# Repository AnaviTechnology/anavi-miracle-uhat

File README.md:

# ANAVI Miracle uHAT

ANAVI Miracle uHAT is an open source hardware Raspberry Pi add-on board for controlling NeoPixel RGB LED strip powered by free and open source software. It features:

* Slot for addressable NeoPixel RGB LED strip like WS2812B, WS2812B, WS2811, etc.
* Power input barrel jack for the addressable RGB LED strip
* Slot for PIR motion sensor
* Slot for I2C mini OLED display
* Slots for up to 3 plug and play I2C sensors for temperature, barometric pressure, humidity and light
* UART (Universal asynchronous receiver/transmitter) pins for debugging
* EEPROM

# License

The project is released under the [Creative Commons Attribution-ShareAlike 4.0 International (CC BY-SA 4.0)](https://creativecommons.org/licenses/by-sa/4.0/).

Note: This is a human-readable summary of (and not a substitute for) the [license](https://creativecommons.org/licenses/by-sa/4.0/legalcode).

You are free to:

Share — copy and redistribute the material in any medium or format Adapt — remix, transform, and build upon the material for any purpose, even commercially. The licensor cannot revoke these freedoms as long as you follow the license terms. Under the following terms:

Attribution — You must give appropriate credit, provide a link to the license, and indicate if changes were made. You may do so in any reasonable manner, but not in any way that suggests the licensor endorses you or your use. ShareAlike — If you remix, transform, or build upon the material, you must distribute your contributions under the same license as the original. No additional restrictions — You may not apply legal terms or technological measures that legally restrict others from doing anything the license permits. Notices:

You do not have to comply with the license for elements of the material in the public domain or where your use is permitted by an applicable exception or limitation. No warranties are given. The license may not give you all of the permissions necessary for your intended use. For example, other rights such as publicity, privacy, or moral rights may limit how you use the material.

You will have to provide a link to the original creator of the project https://www.anavi.technology on any documentation or website.

Credit can be attributed through a link to the creator website: https://www.anavi.technology

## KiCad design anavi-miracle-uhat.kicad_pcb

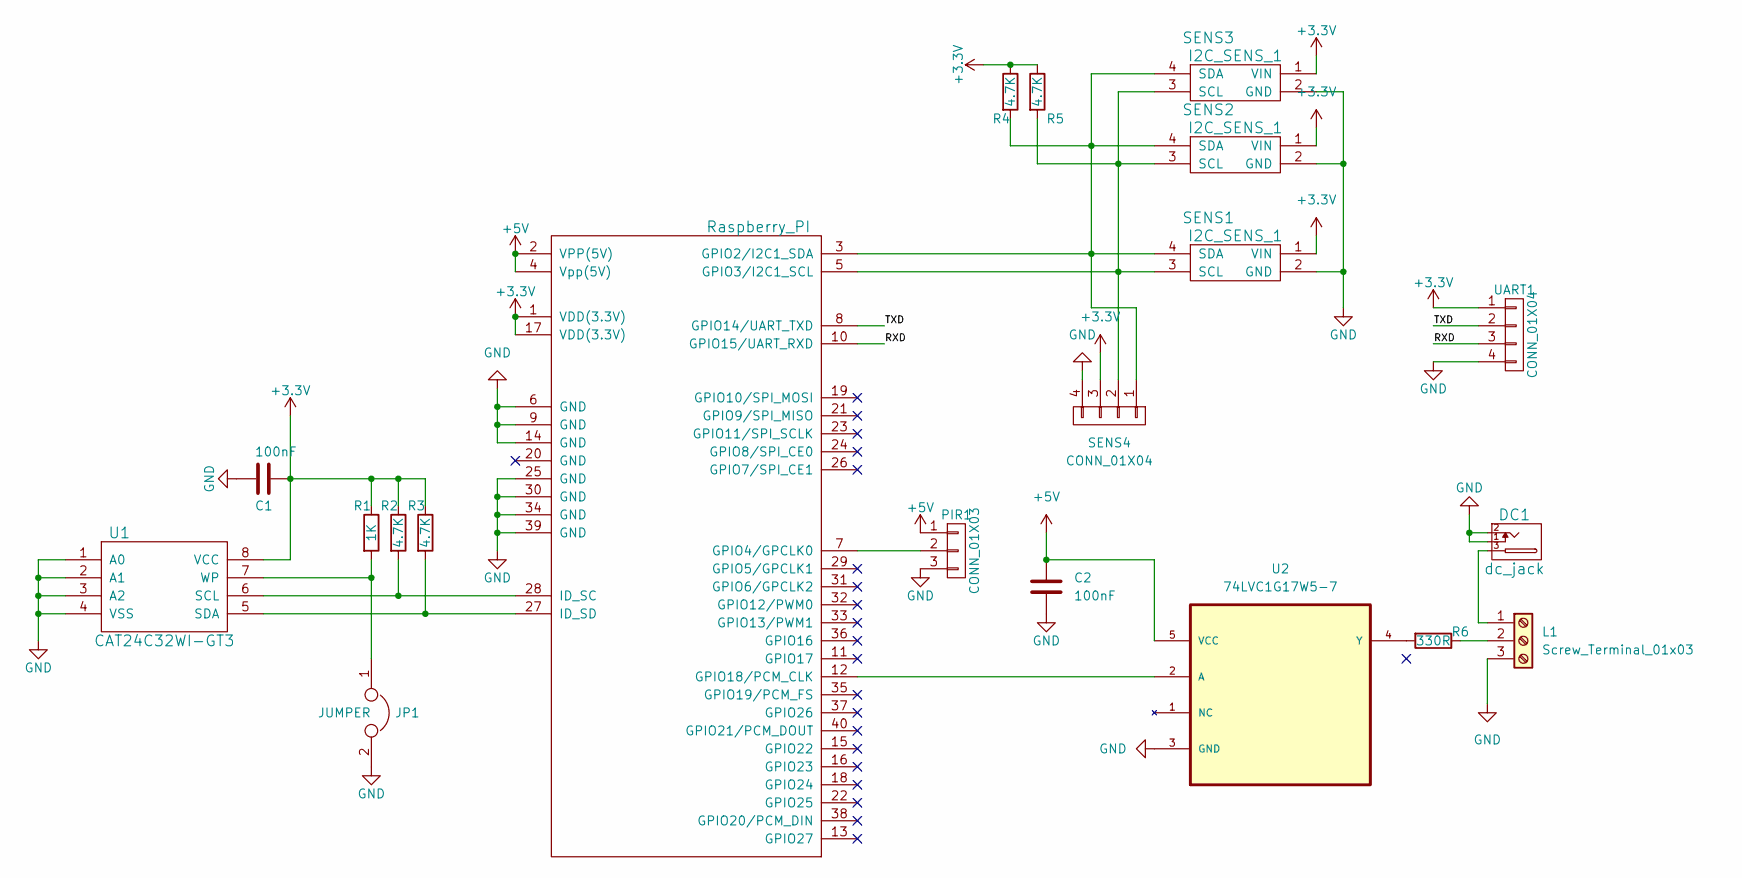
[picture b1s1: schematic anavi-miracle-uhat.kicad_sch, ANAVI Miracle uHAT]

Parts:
C1, C2: 100nF; C_0603_1608Metric_Pad1.08x0.95mm_HandSolder
DC1: dc_jack; dc_socket
JP1: JUMPER; PinHeader_1x02_P2.54mm_Vertical
L1: Screw_Terminal_01x03; TerminalBlock_Phoenix_MKDS-1,5-3_1x03_P5.00mm_Horizontal
PIR1: CONN_01X03; PinHeader_1x03_P2.54mm_Vertical
R1: 1K; R_0603_HandSoldering
R2, R3, R4, R5: 4.7K; R_0603_HandSoldering
R6: 330R; R_0603_1608Metric_Pad0.98x0.95mm_HandSolder
RASP_CONN1: Raspberry_PI; PinHeader_2x20_P2.54mm_Vertical
SENS1, SENS2, SENS3: I2C_SENS_1; PinHeader_1x04_P2.54mm_Vertical
SENS4: CONN_01X04; PinHeader_1x04_P2.54mm_Vertical
U1: CAT24C32WI-GT3; DIP-8_W7.62mm
U2: 74LVC1G17W5-7; SOT95P280X145-5N; MPN 74LVC1G17W5-7
UART1: CONN_01X04; PinHeader_1x04_P2.54mm_Vertical

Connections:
+3V3: C1.1, R1.1, R2.1, R3.1, R4.1, R5.1, RASP_CONN1.1 (VDD(3.3V)), RASP_CONN1.17 (VDD(3.3V)), SENS1.1 (VIN), SENS2.1 (VIN), SENS3.1 (VIN), SENS4.3, U1.8 (VCC), UART1.1; also elsewhere on the board
+5V: C2.1, PIR1.1, RASP_CONN1.2 (VPP(5V)), RASP_CONN1.4 (Vpp(5V)), U2.5 (VCC); also elsewhere on the board
/RXD: RASP_CONN1.10 (GPIO15/UART_RXD), UART1.3; also elsewhere on the board
/TXD: RASP_CONN1.8 (GPIO14/UART_TXD), UART1.2; also elsewhere on the board
GND: C1.2, C2.2, DC1.1, DC1.2, JP1.2, L1.3, PIR1.3, RASP_CONN1.6 (GND), RASP_CONN1.9 (GND), RASP_CONN1.14 (GND), RASP_CONN1.25 (GND), RASP_CONN1.30 (GND), RASP_CONN1.34 (GND), RASP_CONN1.39 (GND), SENS1.2 (GND), SENS2.2 (GND), SENS3.2 (GND), SENS4.4, U1.1 (A0), U1.2 (A1), U1.3 (A2), U1.4 (VSS), U2.3 (GND), UART1.4; also elsewhere on the board
unnamed: DC1.3, L1.1
unnamed: JP1.1, R1.2, U1.7 (WP)
unnamed: L1.2, R6.1
unnamed 8: PIR1.2, RASP_CONN1.7 (GPIO4/GPCLK0); also elsewhere on the board
unnamed: R2.2, RASP_CONN1.28 (ID_SC), U1.6 (SCL)
unnamed: R3.2, RASP_CONN1.27 (ID_SD), U1.5 (SDA)
unnamed: R4.2, RASP_CONN1.3 (GPIO2/I2C1_SDA), SENS1.4 (SDA), SENS2.4 (SDA), SENS3.4 (SDA), SENS4.1
unnamed: R5.2, RASP_CONN1.5 (GPIO3/I2C1_SCL), SENS1.3 (SCL), SENS2.3 (SCL), SENS3.3 (SCL), SENS4.2
unnamed: R6.2, U2.4 (Y)
unnamed: RASP_CONN1.12 (GPIO18/PCM_CLK), U2.2 (A)

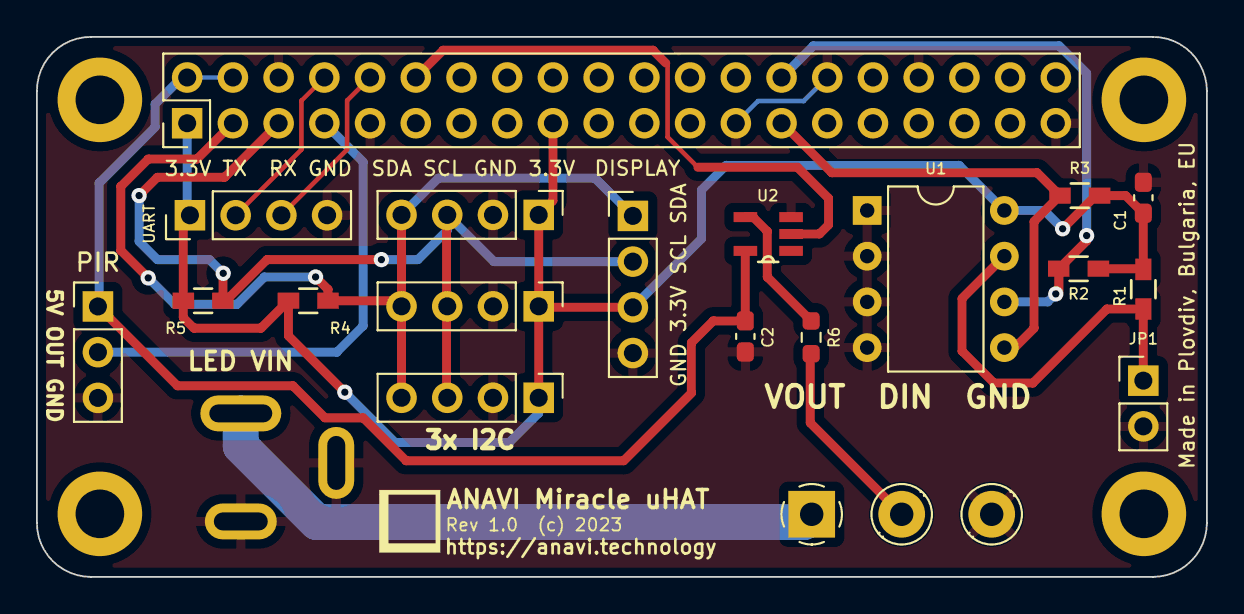
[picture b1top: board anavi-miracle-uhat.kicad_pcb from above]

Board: 2 copper layers, 65.0 x 30.0 mm, 24 parts (0 on the bottom side), 15 nets.

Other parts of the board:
PIR: CONN_01X03; PinHeader_1x03_P2.54mm_Vertical
REF1, REF2, REF3, REF4: MountingHole_2.7mm_M2.5_DIN965_Pad
UART: CONN_01X04; PinHeader_1x04_P2.54mm_Vertical

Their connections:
+3V3: UART.1; also elsewhere on the board
+5V: PIR.1; also elsewhere on the board
/RXD: UART.3; also elsewhere on the board
/TXD: UART.2; also elsewhere on the board
GND: PIR.3, UART.4; also elsewhere on the board
unnamed 8: PIR.2; also elsewhere on the board

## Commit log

2023-04-12 ANAVI Miracle uHAT: Initial commit
    Raspberry Pi add-on board for an addressable LED strip.
2023-04-14 .gitignore: Ignore backups
    Ignore KiCad backup files.
2023-04-14 anavi-miracle-uhat: Adjust LED strip connector
    Adjust the addressable LED strip connector.
2023-05-07 anavi-miracle-uhat.kicad_pcb: Labels
    Adjust labels on front silkscreen.
2023-08-11 anavi-miracle-uhat: Add assembly notes
    Add assembly notes to the front fabrication layer.

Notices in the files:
anavi-miracle-uhat.kicad_pcb:
Rev 1.0  (c) 2023
